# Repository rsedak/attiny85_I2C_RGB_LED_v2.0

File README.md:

[Croatian version](README_HR-HR.md).

Introduction
============

Purpose of ATtiny85 I2C RGB LED module is student education. It shows how to controll RGB via I2C protocol.

Contributor
------------
- Robert Sedak — features, programming, schematic design, CAD design.

Application
-----------
Robert Sedak made a video with example programmed in Arduino IDE with ATtiny85 support:

You can download example for Arduino IDE from [here](firmware/).

Bill Of Materials
-----------------
- 1 ea., PCB
- 2 ea., 560R ohm 1/4W 1% Resistor (R1, R3)
- 1 ea., 620R ohm 1/4W 1% Resistor (R2)
- 2 ea., 4.7K ohm 1/4W 1% Resistor (R4, R5)
- 1 ea., RGB LED 5mm (D1)
- 1 ea., 100nF 50V Monolithic Ceramic Capacitor (C1)
- 1 ea., 8-Pin DIL IC Socket
- 1 ea., ATtiny85 (U1)
- 1 ea., 1x4 pin 2.54mm Pin Header (J1)

Design Files
------------
This project is designed using Open Source [KiCad](http://kicad.org/). Design files are located in the [design_files](design_files/) folder.  You can see the [schematic](images/attiny85_I2C_RGB_LED_v2_schematic.png).

Gerber files
------------
You can download gerber files from [here](gerber/attiny85_I2C_RGB_LED_v2.zip).

Firmware
--------
This project can be programmed using the Open Source [Arduino](https://www.arduino.cc/).
[ATTinyCore by Spence Konde](https://github.com/SpenceKonde/ATTinyCore) was used to program ATtiny85 in Arduino IDE.
Arduino example is located in [examples](firmware/) folder.

License
-------
[Attribution-ShareAlike 4.0 International (CC BY-SA 4.0)](https://creativecommons.org/licenses/by-sa/4.0/)

You are free to:
- Share — copy and redistribute the material in any medium or format
- Adapt — remix, transform, and build upon the material

This license is acceptable for Free Cultural Works.
- The licensor cannot revoke these freedoms as long as you follow the license terms.

Under the following terms:
- Attribution — You must give appropriate credit, provide a link to the license, and indicate if changes were made. You may do so in any reasonable manner, but not in any way that suggests the licensor endorses you or your use.
- ShareAlike — If you remix, transform, or build upon the material, you must distribute your contributions under the same license as the original.

No additional restrictions — You may not apply legal terms or technological measures that legally restrict others from doing anything the license permits.

Reference Designs ARE PROVIDED "AS IS" AND "WITH ALL FAULTS". Authors DISCLAIMS ALL OTHER WARRANTIES, EXPRESS OR IMPLIED, REGARDING PRODUCTS, INCLUDING BUT NOT LIMITED TO, ANY IMPLIED WARRANTIES OF MERCHANTABILITY OR FITNESS FOR A PARTICULAR PURPOSE.
Authors may make changes to specifications and product descriptions at any time, without notice. The Customer must notrely on the absence or characteristics of any features or instructions marked "reserved" or "undefined."
Authors reservesthese for future definition and shall have no responsibility whatsoever for conflicts or incompatibilities arising from future changes to them. The product information on the Web Site or Materials is subject to change without notice. Do not finalize a design with this info.

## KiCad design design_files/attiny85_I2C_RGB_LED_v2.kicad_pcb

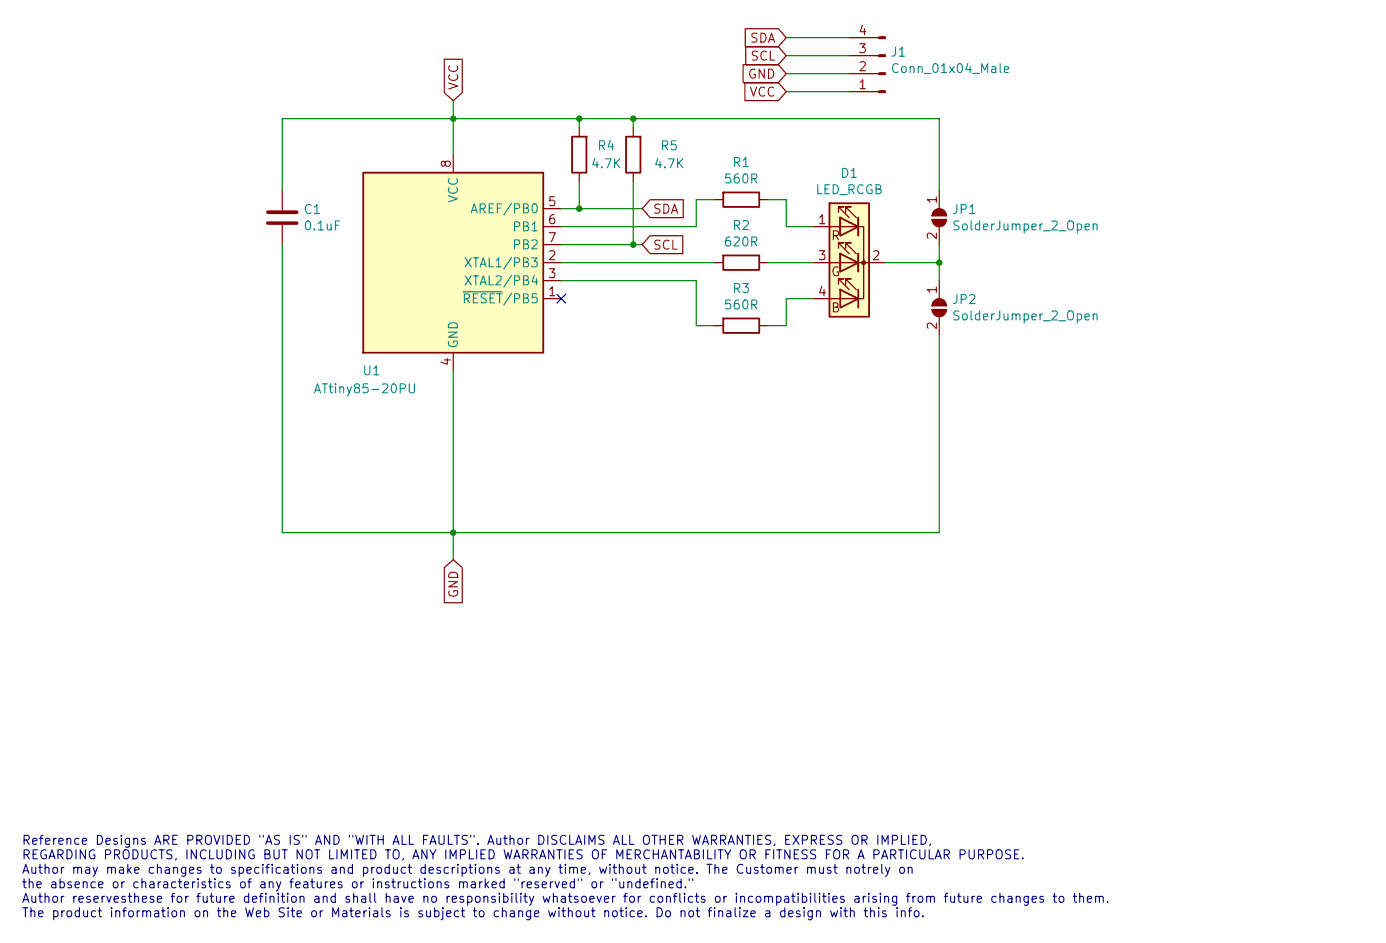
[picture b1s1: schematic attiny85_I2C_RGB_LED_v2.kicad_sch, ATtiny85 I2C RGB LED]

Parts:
C1: 0.1uF; C_Rect_L4.6mm_W2.0mm_P2.50mm_MKS02_FKP02
D1: LED_RCGB; LED_D5.0mm-4_RGB
J1: Conn_01x04_Male; PinHeader_1x04_P2.54mm_Vertical
JP1, JP2: SolderJumper_2_Open; SolderJumper-2_P1.3mm_Open_RoundedPad1.0x1.5mm
R1, R3: 560R; R_Axial_DIN0207_L6.3mm_D2.5mm_P7.62mm_Horizontal
R2: 620R; R_Axial_DIN0207_L6.3mm_D2.5mm_P7.62mm_Horizontal
R4, R5: 4.7K; R_Axial_DIN0207_L6.3mm_D2.5mm_P7.62mm_Horizontal
U1: ATtiny85-20PU; DIP-8_W7.62mm

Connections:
GND: C1.2, J1.2, JP2.2 (B), U1.4 (GND)
unnamed: D1.1 (RA), R1.1
unnamed: D1.2 (K), JP1.2 (B), JP2.1 (A)
unnamed: D1.3 (GA), R2.1
unnamed: D1.4 (BA), R3.1
unnamed: R1.2, U1.6 (PB1)
unnamed: R2.2, U1.2 (XTAL1/PB3)
unnamed: R3.2, U1.3 (XTAL2/PB4)
SCL: J1.3, R5.1, U1.7 (PB2)
SDA: J1.4, R4.1, U1.5 (AREF/PB0)
VCC: C1.1, J1.1, JP1.1 (A), R4.2, R5.2, U1.8 (VCC)

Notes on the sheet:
Reference Designs ARE PROVIDED "AS IS" AND "WITH ALL FAULTS". Author DISCLAIMS ALL OTHER WARRANTIES, EXPRESS OR IMPLIED, REGARDING PRODUCTS, INCLUDING BUT NOT LIMITED TO, ANY IMPLIED WARRANTIES OF MERCHANTABILITY OR FITNESS FOR A PARTICULAR PURPOSE. Author may make changes to specifications and pro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

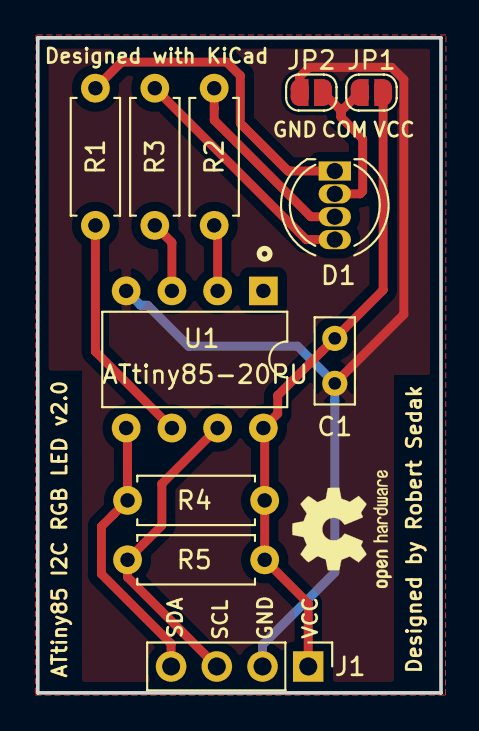
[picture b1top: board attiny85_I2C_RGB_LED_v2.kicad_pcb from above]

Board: 2 copper layers, 22.4 x 36.4 mm, 11 parts (0 on the bottom side), 11 nets.

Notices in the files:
design_files/attiny85_I2C_RGB_LED_v2.kicad_sch:
License: CC-BY-SA 4.0
